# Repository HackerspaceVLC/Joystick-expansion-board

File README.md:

# Joystick-expansion-board

Joystick de 4 jugadores basado en Arduino Leonardo para el Hackerspace. 

Usa parte de las opciones de https://github.com/MHeironimus/ArduinoJoystickLibrary y la documentación que ya no esta disponible en imaginaryindustries.com

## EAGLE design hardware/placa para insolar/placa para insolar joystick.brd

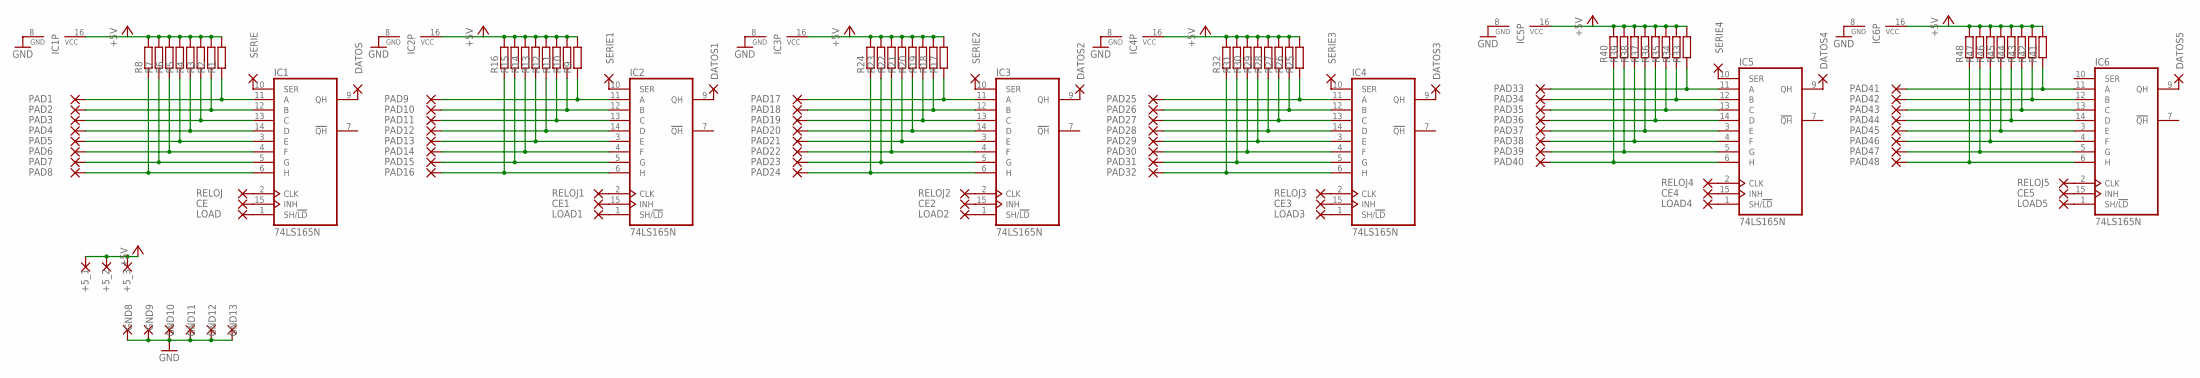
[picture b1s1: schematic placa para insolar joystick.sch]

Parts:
+5_1, +5_2, +5_3: WIREPAD2,54/1,0; 2,54/1,0
CE, CE1, CE2, CE3, CE4, CE5: WIREPAD2,54/1,0; 2,54/1,0
DATOS, DATOS1, DATOS2, DATOS3, DATOS4, DATOS5: WIREPAD2,54/1,0; 2,54/1,0
GND8, GND9, GND10, GND11, GND12, GND13: WIREPAD2,54/1,0; 2,54/1,0
IC1, IC2, IC3, IC4, IC5, IC6: 74LS165N; DIL16
LOAD, LOAD1, LOAD2, LOAD3, LOAD4, LOAD5: WIREPAD2,54/1,0; 2,54/1,0
PAD1, PAD2, PAD3, PAD4, PAD5, PAD6, PAD7, PAD8, PAD9, PAD10, PAD11, PAD12, PAD13, PAD14, PAD15, PAD16, PAD17, PAD18, PAD19, PAD20, PAD21, PAD22, PAD23, PAD24, PAD25, PAD26, PAD27, PAD28, PAD29, PAD30, PAD31, PAD32, PAD33, PAD34, PAD35, PAD36, PAD37, PAD38, PAD39, PAD40, PAD41, PAD42, PAD43, PAD44, PAD45, PAD46, PAD47, PAD48: WIREPAD2,54/1,0; 2,54/1,0
R1, R2, R3, R4, R5, R6, R7, R8, R9, R10, R11, R12, R13, R14, R15, R16, R17, R18, R19, R20, R21, R22, R23, R24, R25, R26, R27, R28, R29, R30, R31, R32, R33, R34, R35, R36, R37, R38, R39, R40, R41, R42, R43, R44, R45, R46, R47, R48: R-EU_0204/7; 0204/7
RELOJ, RELOJ1, RELOJ2, RELOJ3, RELOJ4, RELOJ5: WIREPAD2,54/1,0; 2,54/1,0
SERIE, SERIE1, SERIE2, SERIE3, SERIE4: WIREPAD2,54/1,0; 2,54/1,0

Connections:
+5V: +5_1.1, +5_2.1, +5_3.1, IC1.16 (VCC), IC2.16 (VCC), IC3.16 (VCC), IC4.16 (VCC), IC5.16 (VCC), IC6.16 (VCC), R1.2, R2.2, R3.2, R4.2, R5.2, R6.2, R7.2, R8.2, R9.2, R10.2, R11.2, R12.2, R13.2, R14.2, R15.2, R16.2, R17.2, R18.2, R19.2, R20.2, R21.2, R22.2, R23.2, R24.2, R25.2, R26.2, R27.2, R28.2, R29.2, R30.2, R31.2, R32.2, R33.2, R34.2, R35.2, R36.2, R37.2, R38.2, R39.2, R40.2, R41.2, R42.2, R43.2, R44.2, R45.2, R46.2, R47.2, R48.2
GND: GND8.1, GND9.1, GND10.1, GND11.1, GND12.1, GND13.1, IC1.8 (GND), IC2.8 (GND), IC3.8 (GND), IC4.8 (GND), IC5.8 (GND), IC6.8 (GND)
unnamed: IC1.11 (A), PAD1.1, R1.1
unnamed: IC1.12 (B), PAD2.1, R2.1
unnamed: IC1.13 (C), PAD3.1, R3.1
unnamed: IC1.14 (D), PAD4.1, R4.1
unnamed: IC1.3 (E), PAD5.1, R5.1
unnamed: IC1.4 (F), PAD6.1, R6.1
unnamed: IC1.5 (G), PAD7.1, R7.1
unnamed: IC1.6 (H), PAD8.1, R8.1
unnamed: IC2.11 (A), PAD9.1, R9.1
unnamed: IC2.12 (B), PAD10.1, R10.1
unnamed: IC2.13 (C), PAD11.1, R11.1
unnamed: IC2.14 (D), PAD12.1, R12.1
unnamed: IC2.3 (E), PAD13.1, R13.1
unnamed: IC2.4 (F), PAD14.1, R14.1
unnamed: IC2.5 (G), PAD15.1, R15.1
unnamed: IC2.6 (H), PAD16.1, R16.1
unnamed: IC3.11 (A), PAD17.1, R17.1
unnamed: IC3.12 (B), PAD18.1, R18.1
unnamed: IC3.13 (C), PAD19.1, R19.1
unnamed: IC3.14 (D), PAD20.1, R20.1
unnamed: IC3.3 (E), PAD21.1, R21.1
unnamed: IC3.4 (F), PAD22.1, R22.1
unnamed: IC3.5 (G), PAD23.1, R23.1
unnamed: IC3.6 (H), PAD24.1, R24.1
unnamed: IC4.11 (A), PAD25.1, R25.1
unnamed: IC4.12 (B), PAD26.1, R26.1
unnamed: IC4.13 (C), PAD27.1, R27.1
unnamed: IC4.14 (D), PAD28.1, R28.1
unnamed: IC4.3 (E), PAD29.1, R29.1
unnamed: IC4.4 (F), PAD30.1, R30.1
unnamed: IC4.5 (G), PAD31.1, R31.1
unnamed: IC4.6 (H), PAD32.1, R32.1
unnamed: IC5.11 (A), PAD33.1, R33.1
unnamed: IC5.12 (B), PAD34.1, R34.1
unnamed: IC5.13 (C), PAD35.1, R35.1
unnamed: IC5.14 (D), PAD36.1, R36.1
unnamed: IC5.3 (E), PAD37.1, R37.1
unnamed: IC5.4 (F), PAD38.1, R38.1
unnamed: IC5.5 (G), PAD39.1, R39.1
unnamed: IC5.6 (H), PAD40.1, R40.1
unnamed: IC6.11 (A), PAD41.1, R41.1
unnamed: IC6.12 (B), PAD42.1, R42.1
unnamed: IC6.13 (C), PAD43.1, R43.1
unnamed: IC6.14 (D), PAD44.1, R44.1
unnamed: IC6.3 (E), PAD45.1, R45.1
unnamed: IC6.4 (F), PAD46.1, R46.1
unnamed: IC6.5 (G), PAD47.1, R47.1
unnamed: IC6.6 (H), PAD48.1, R48.1
unnamed: IC1.2 (CLK), RELOJ.1
unnamed: CE.1, IC1.15 (INH)
unnamed: IC1.1 (SH/!LD), LOAD.1
unnamed: IC2.2 (CLK), RELOJ1.1
unnamed: CE1.1, IC2.15 (INH)
unnamed: IC2.1 (SH/!LD), LOAD1.1
unnamed: IC3.2 (CLK), RELOJ2.1
unnamed: CE2.1, IC3.15 (INH)
unnamed: IC3.1 (SH/!LD), LOAD2.1
unnamed: IC4.2 (CLK), RELOJ3.1
unnamed: CE3.1, IC4.15 (INH)
unnamed: IC4.1 (SH/!LD), LOAD3.1
unnamed: IC5.2 (CLK), RELOJ4.1
unnamed: CE4.1, IC5.15 (INH)
unnamed: IC5.1 (SH/!LD), LOAD4.1
unnamed: IC6.2 (CLK), RELOJ5.1
unnamed: CE5.1, IC6.15 (INH)
unnamed: IC6.1 (SH/!LD), LOAD5.1
unnamed: DATOS5.1, IC6.9 (QH)
unnamed: IC5.10 (SER), SERIE4.1
unnamed: DATOS4.1, IC5.9 (QH)
unnamed: DATOS3.1, IC4.9 (QH)
unnamed: IC4.10 (SER), SERIE3.1
unnamed: DATOS2.1, IC3.9 (QH)
unnamed: IC3.10 (SER), SERIE2.1
unnamed: DATOS1.1, IC2.9 (QH)
unnamed: IC2.10 (SER), SERIE1.1
unnamed: DATOS.1, IC1.9 (QH)
unnamed: IC1.10 (SER), SERIE.1

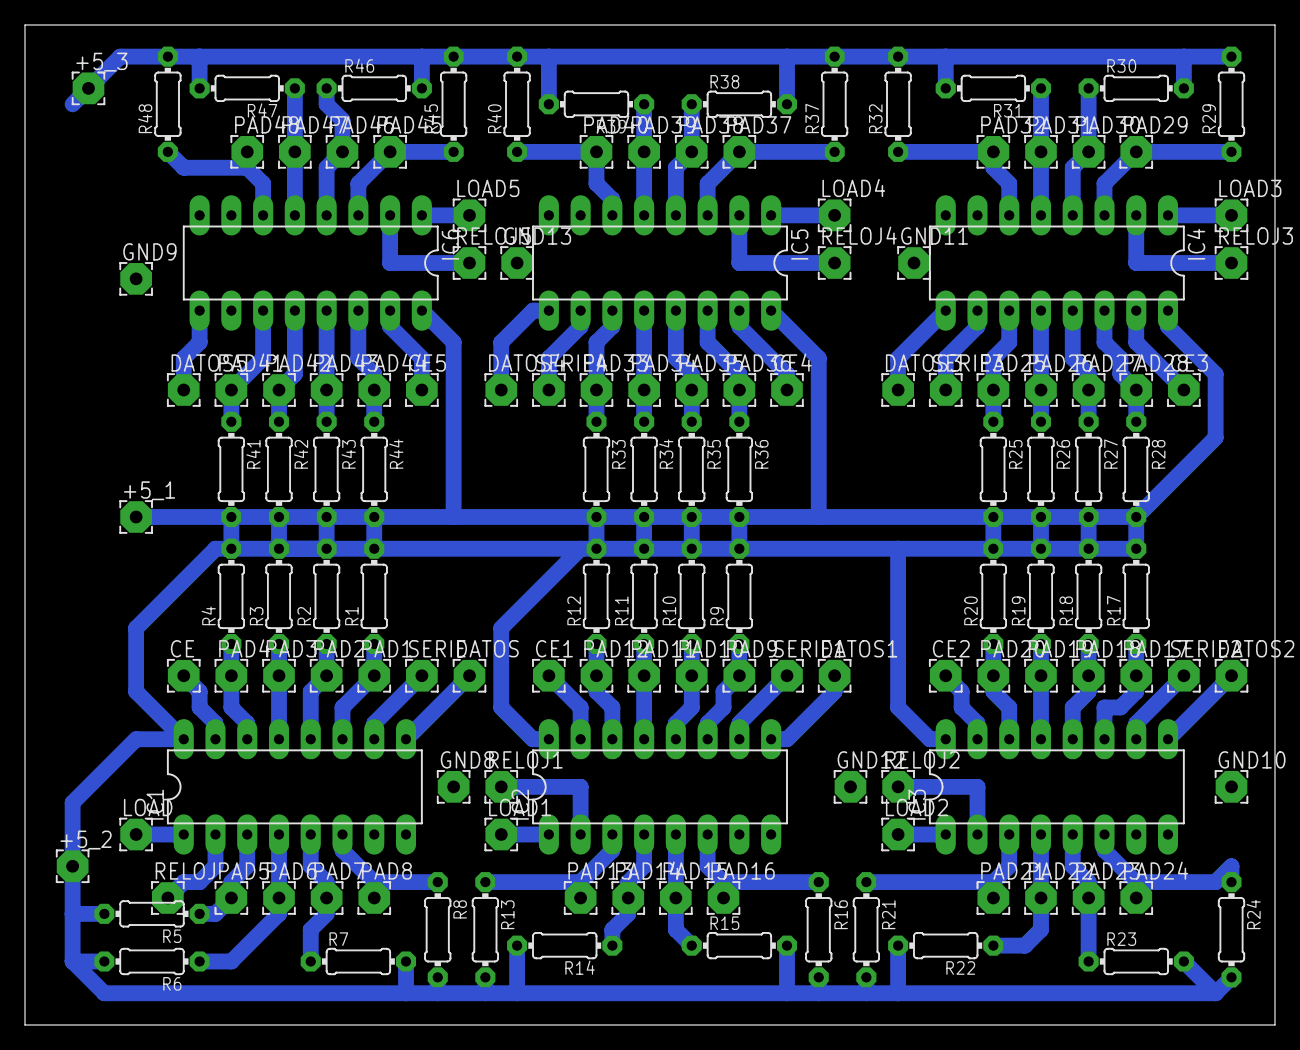
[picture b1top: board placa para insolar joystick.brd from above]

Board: 2 copper layers, 100.0 x 80.0 mm, 140 parts (0 on the bottom side), 79 nets.

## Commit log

2016-02-09 Primera subida
2016-06-07 retoques a la placa para insolar. parece que esta lista...
2016-06-07 reestructurar carpetas
2017-04-18 Starting Pcb for fab
2017-04-20 comienzo la pcb, sch casi acabado
